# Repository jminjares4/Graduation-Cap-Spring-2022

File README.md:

# Graduation Cap Spring 2022 :zap:

## **Description**
This upcoming May, I will be graduating with my **Master of Science in Computer Engineering** from [The University of Texas at El Paso](https://www.utep.edu/engineering/ece/index.html)! Therefore, I decided to create a custom graduation cap to decorate as a true *engineer*. The graduation cap will utlize ARM Cortex M0 microcontroller with addtional sensors, LEDs, and NFC to store data.

## **Firmware**
- [x] Utlize open source Real-Time Operating System: [FreeRTOS]()
- [x] ARM Cortex M0+ micocontroller
- [x] Low power mode
- [x] custom drivers
## **Hardware**
- [x] Fixed USB data lines
  - [x] Update USB &pm; datalines with 90 ohms impedance
- [x] Open source development Electronic Design Automation (EDA): [KiCad]()
- [x] Two layer Printed Circuit Board (PCB)
- [x] Source Components
  - [x] LEDs
  - [x] ADLX335
  - [x] Lithium battery
  - [x] RP2040 custom board
- [x] Developed schematic
- [x] Developed printed circuit board
- [x] Board layout 4.74" * 4.74" with 45 degree rotation

## **Graduation Cap**

## **Development**
|**Software** | **Microcontroller** | **Hardware Design** |
| :---:    | :---:            | :---:                               |
| |  |  |

## **Author:**
* [**Jesus Minjares**](https://github.com/jminjares4)<br>
  * Master of Science in Computer Engineering<br>

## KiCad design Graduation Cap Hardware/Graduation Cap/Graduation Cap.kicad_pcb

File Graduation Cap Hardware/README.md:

# Graduation Cap Spring 2022 :zap:
## **Description**

The graduation cap was developed KiCad.

## **Hardware**
- [x] Open source development Electronic Design Automation (EDA): [KiCad]()
- [x] Two layer Printed Circuit Board (PCB)
- [x] Source Components
  - [x] LEDs
  - [x] ADLX335
  - [x] Lithium battery
  - [x] RP2040 custom board
- [x] Developed schematic
- [x] Developed printed circuit board
- [x] Board layout 4.74" * 4.7" with 45 degree rotation

## **Graduation Schematic**

## **Graduation Cap PCB**

## **Author:**
* [**Jesus Minjares**](https://github.com/jminjares4)<br>
  * Master of Science in Computer Engineering<br>

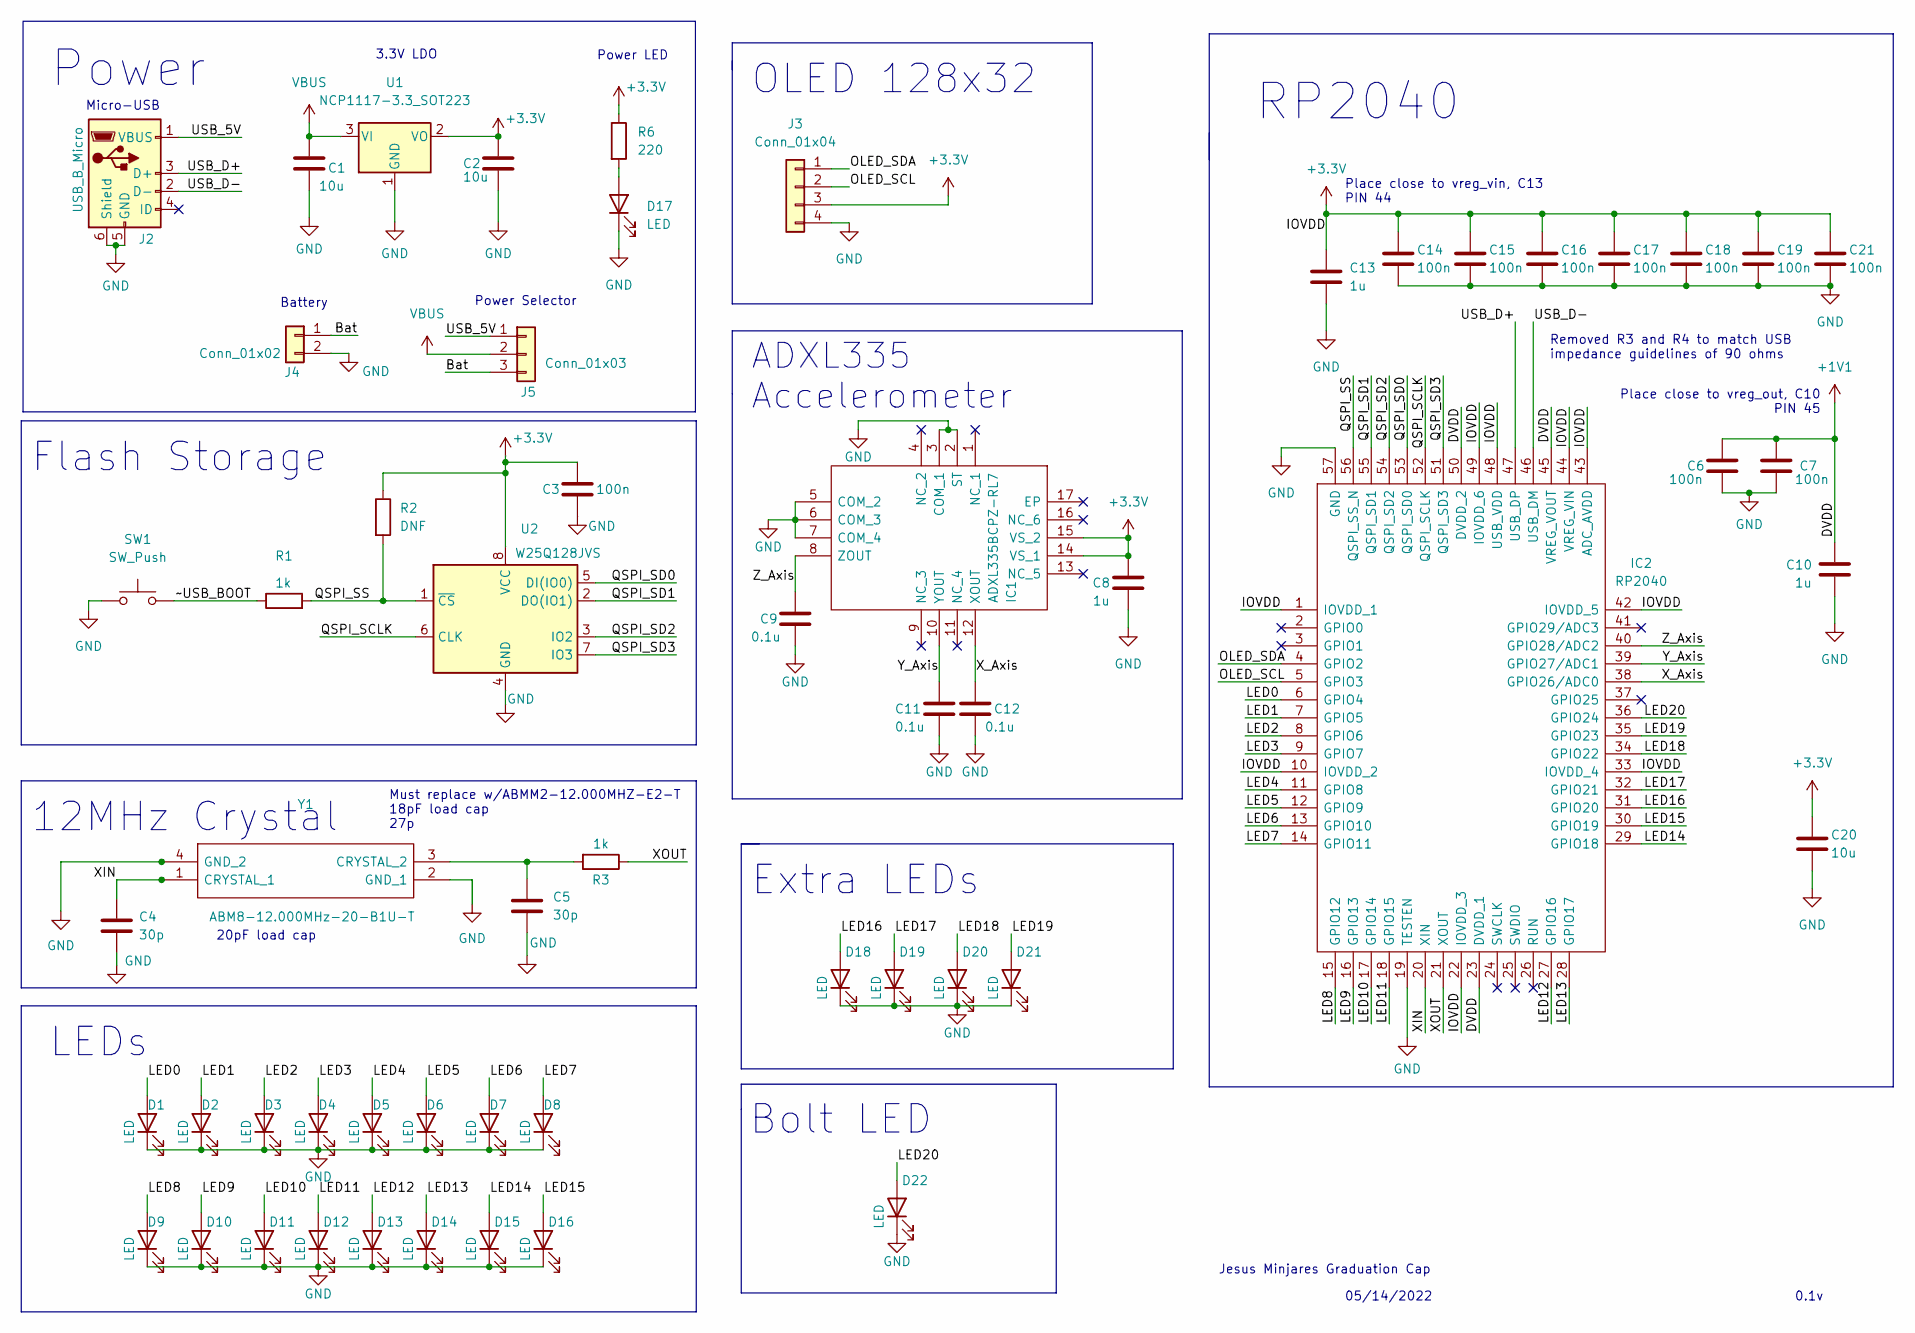
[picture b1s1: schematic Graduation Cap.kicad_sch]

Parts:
C1, C2: 10u; C_0603_1608Metric
C3, C6, C7, C14, C15, C16, C17, C18, C19, C21: 100n; C_0402_1005Metric
C4, C5: 30p; C_0402_1005Metric
C8: 1u; C_0603_1608Metric
C9, C11, C12: 0.1u; C_0402_1005Metric
C10, C13: 1u; C_0402_1005Metric
C20: 10u; C_0402_1005Metric
D1, D2, D3, D4, D5, D6, D7, D8, D9, D10, D11, D12, D13, D14, D15, D16, D17, D18, D19, D20, D21: LED; LED_0805_2012Metric
D22: LED; LED_0402_1005Metric
IC1: ADXL335BCPZ-RL7; QFN65P400X400X150-17N-D; Manufacturer_Part_Number ADXL335BCPZ-RL7; Mouser Part Number 584-ADXL335BCPZ-R7
IC2: RP2040; QFN40P700X700X90-57N-D; Manufacturer_Part_Number RP2040
J2: USB_B_Micro; USB_Micro-B_Molex_47346-0001
J3: Conn_01x04; PinSocket_1x04_P2.54mm_Vertical
J4: Conn_01x02; JST_PH_S2B-PH-K_1x02_P2.00mm_Horizontal
J5: Conn_01x03; PinHeader_1x03_P2.54mm_Vertical
R1, R3: 1k; R_0402_1005Metric
R2: DNF; R_0402_1005Metric
R6: 220; R_0603_1608Metric
SW1: SW_Push; SW_PUSH_6mm
U1: NCP1117-3.3_SOT223; SOT-223-3_TabPin2
U2: W25Q128JVS; SOIC-8_5.23x5.23mm_P1.27mm
Y1: ABM8-12.000MHz-20-B1U-T; ABM812000MHz20B1UT; Manufacturer_Part_Number ABM8-12.000MHz-20-B1U-T; Mouser Part Number 815-M812000MHZ20B1UT

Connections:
+1V1: C6.1, C7.1, C10.1, IC2.23 (DVDD_1), IC2.45 (VREG_VOUT), IC2.50 (DVDD_2)
+3V3: C2.1, C3.1, C8.2, C13.1, C14.1, C15.1, C16.1, C17.1, C18.1, C19.1, C20.1, C21.1, IC1.14 (VS_1), IC1.15 (VS_2), IC2.1 (IOVDD_1), IC2.10 (IOVDD_2), IC2.22 (IOVDD_3), IC2.33 (IOVDD_4), IC2.42 (IOVDD_5), IC2.43 (ADC_AVDD), IC2.44 (VREG_VIN), IC2.48 (USB_VDD), IC2.49 (IOVDD_6), J3.3, R2.1, R6.1, U1.2 (VO), U2.8 (VCC)
/Bat: J4.1, J5.3
/LED0: D1.2 (A), IC2.6 (GPIO4)
/LED1: D2.2 (A), IC2.7 (GPIO5)
/LED2: D3.2 (A), IC2.8 (GPIO6)
/LED3: D4.2 (A), IC2.9 (GPIO7)
/LED4: D5.2 (A), IC2.11 (GPIO8)
/LED5: D6.2 (A), IC2.12 (GPIO9)
/LED6: D7.2 (A), IC2.13 (GPIO10)
/LED7: D8.2 (A), IC2.14 (GPIO11)
/LED8: D9.2 (A), IC2.15 (GPIO12)
/LED9: D10.2 (A), IC2.16 (GPIO13)
/LED10: D11.2 (A), IC2.17 (GPIO14)
/LED11: D12.2 (A), IC2.18 (GPIO15)
/LED12: D13.2 (A), IC2.27 (GPIO16)
/LED13: D14.2 (A), IC2.28 (GPIO17)
/LED14: D15.2 (A), IC2.29 (GPIO18)
/LED15: D16.2 (A), IC2.30 (GPIO19)
/LED16: D18.2 (A), IC2.31 (GPIO20)
/LED17: D19.2 (A), IC2.32 (GPIO21)
/LED18: D20.2 (A), IC2.34 (GPIO22)
/LED19: D21.2 (A), IC2.35 (GPIO23)
/LED20: D22.2 (A), IC2.36 (GPIO24)
/OLED_SCL: IC2.5 (GPIO3), J3.2
/OLED_SDA: IC2.4 (GPIO2), J3.1
/QSPI_SCLK: IC2.52 (QSPI_SCLK), U2.6 (CLK)
/QSPI_SD0: IC2.53 (QSPI_SD0), U2.5 (DI(IO0))
/QSPI_SD1: IC2.55 (QSPI_SD1), U2.2 (DO(IO1))
/QSPI_SD2: IC2.54 (QSPI_SD2), U2.3 (IO2)
/QSPI_SD3: IC2.51 (QSPI_SD3), U2.7 (IO3)
/QSPI_SS: IC2.56 (QSPI_SS_N), R1.2, R2.2, U2.1 (~CS)
/USB_5V: J2.1 (VBUS), J5.1
/USB_D+: IC2.47 (USB_DP), J2.3 (D+)
/USB_D-: IC2.46 (USB_DM), J2.2 (D-)
/XIN: C4.1, IC2.20 (XIN), Y1.1 (CRYSTAL_1)
/XOUT: IC2.21 (XOUT), R3.1
/X_Axis: C12.2, IC1.12 (XOUT), IC2.38 (GPIO26/ADC0)
/Y_Axis: C11.1, IC1.10 (YOUT), IC2.39 (GPIO27/ADC1)
/Z_Axis: C9.1, IC1.8 (ZOUT), IC2.40 (GPIO28/ADC2)
/~USB_BOOT: R1.1, SW1.2
GND: C1.2, C2.2, C3.2, C4.2, C5.2, C6.2, C7.2, C8.1, C9.2, C10.2, C11.2, C12.1, C13.2, C14.2, C15.2, C16.2, C17.2, C18.2, C19.2, C20.2, C21.2, D1.1 (K), D2.1 (K), D3.1 (K), D4.1 (K), D5.1 (K), D6.1 (K), D7.1 (K), D8.1 (K), D9.1 (K), D10.1 (K), D11.1 (K), D12.1 (K), D13.1 (K), D14.1 (K), D15.1 (K), D16.1 (K), D17.1 (K), D18.1 (K), D19.1 (K), D20.1 (K), D21.1 (K), D22.1 (K), IC1.2 (ST), IC1.3 (COM_1), IC1.5 (COM_2), IC1.6 (COM_3), IC1.7 (COM_4), IC2.19 (TESTEN), IC2.57 (GND), J2.5 (GND), J2.6 (Shield), J3.4, J4.2, SW1.1, U1.1 (GND), U2.4 (GND), Y1.2 (GND_1), Y1.4 (GND_2)
unnamed: C5.1, R3.2, Y1.3 (CRYSTAL_2)
unnamed: D17.2 (A), R6.2
VBUS: C1.1, J5.2, U1.3 (VI)

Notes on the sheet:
Place close to vreg_vin, C13 PIN 44
Micro-USB
Power
05/14/2022
Must replace w/ABMM2-12.000MHZ-E2-T 18pF load cap 27p
Jesus Minjares Graduation Cap
RP2040
3.3V LDO
Power Selector
20pF load cap
ADXL335 Accelerometer
0.1v
OLED 128x32
Extra LEDs
Place close to vreg_out, C10 PIN 45
Removed R3 and R4 to match USB impedance guidelines of 90 ohms
Bolt LED
Flash Storage
LEDs
Battery
Power LED
12MHz Crystal

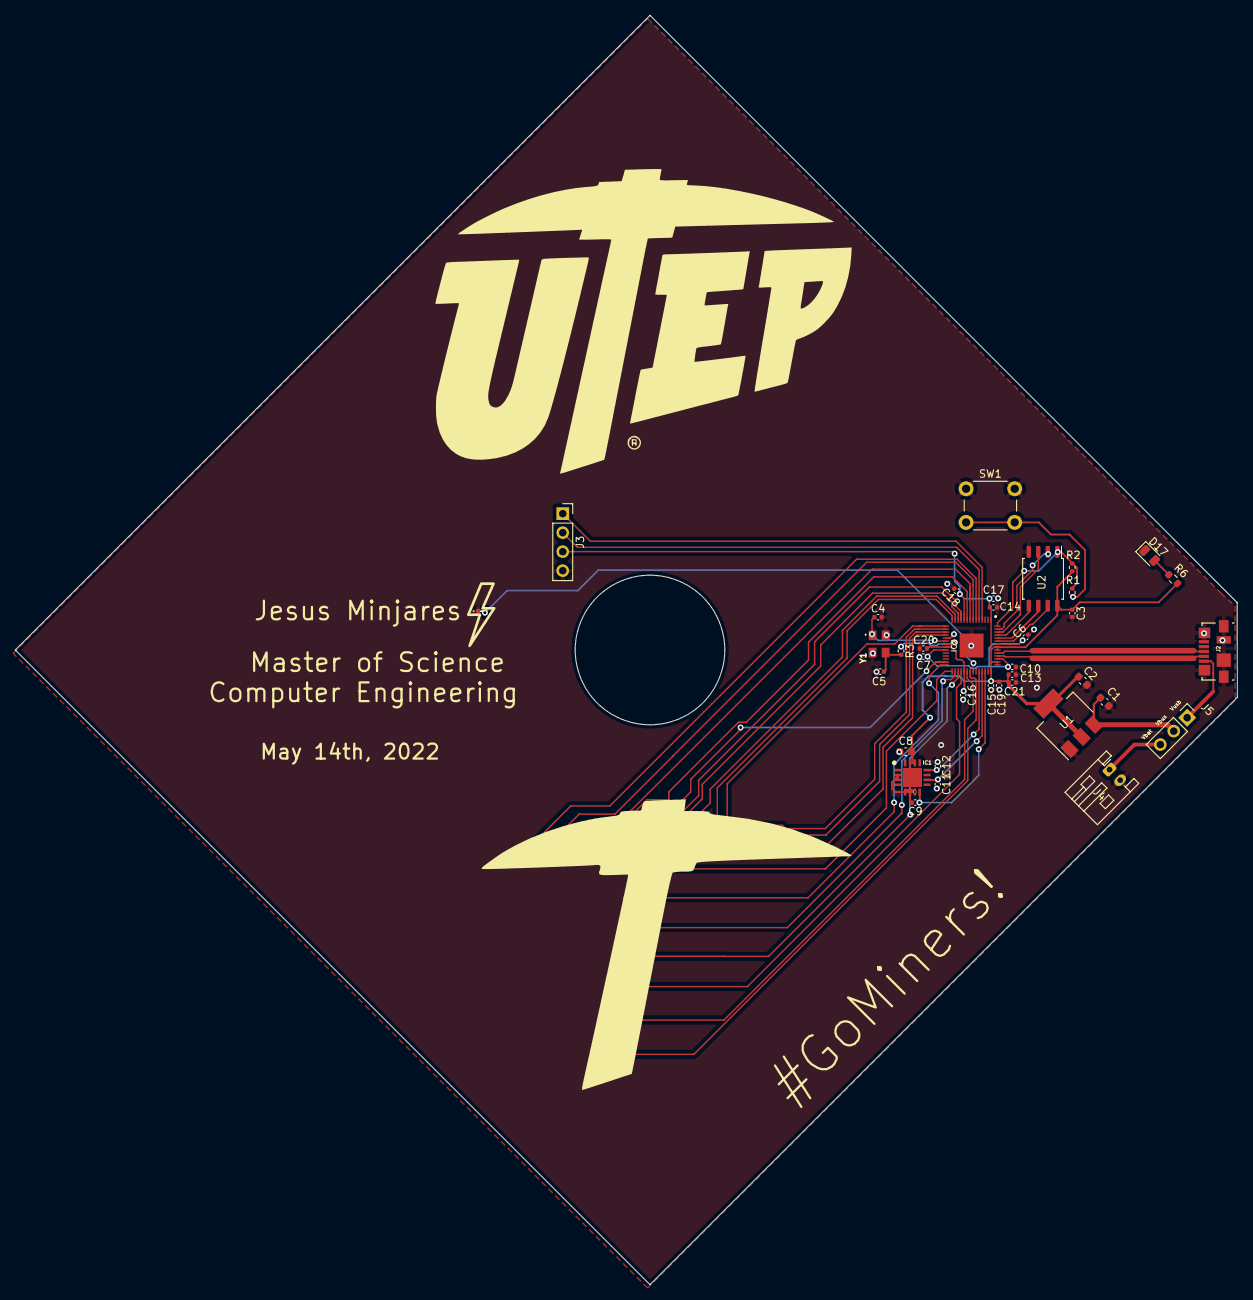
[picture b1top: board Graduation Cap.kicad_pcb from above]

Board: 2 copper layers, 163.4 x 169.7 mm, 57 parts (0 on the bottom side), 45 nets.

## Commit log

2022-03-17 Added gitignore
2022-03-17 Added firmware
2022-03-17 Added gitmodules
2022-03-17 Added build
2022-03-17 Remove build
2022-03-17 Added gitignore for firmware
2022-03-17 Update gitignore
2022-03-26 Added kicad rendering
2022-03-26 Added gif to readme
2022-04-02 Added hardware directory"
2022-04-03 Added custom structures: bolt, accelerometer, and pickaxe
2022-05-16 Added hardware
2022-05-16 Moved readme
2022-05-16 Added latest images of graduation cap
2022-05-16 Fix schematic
2022-05-16 Added new images
2022-05-16 Updated hardware finished requirements
2022-06-10 Updated pcb
2022-06-10 Updated readme with latest gif and schematic
2022-06-10 Updated images to the latest version of board
2022-06-10 Updated schematic and pcb layout
2022-06-10 Updated gif
2022-06-10 Added development badges
